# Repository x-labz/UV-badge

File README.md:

# UV-badge

Project site on hackaday.io https://hackaday.io/project/4706-uv-badge 

Twitter: @xLabzNet

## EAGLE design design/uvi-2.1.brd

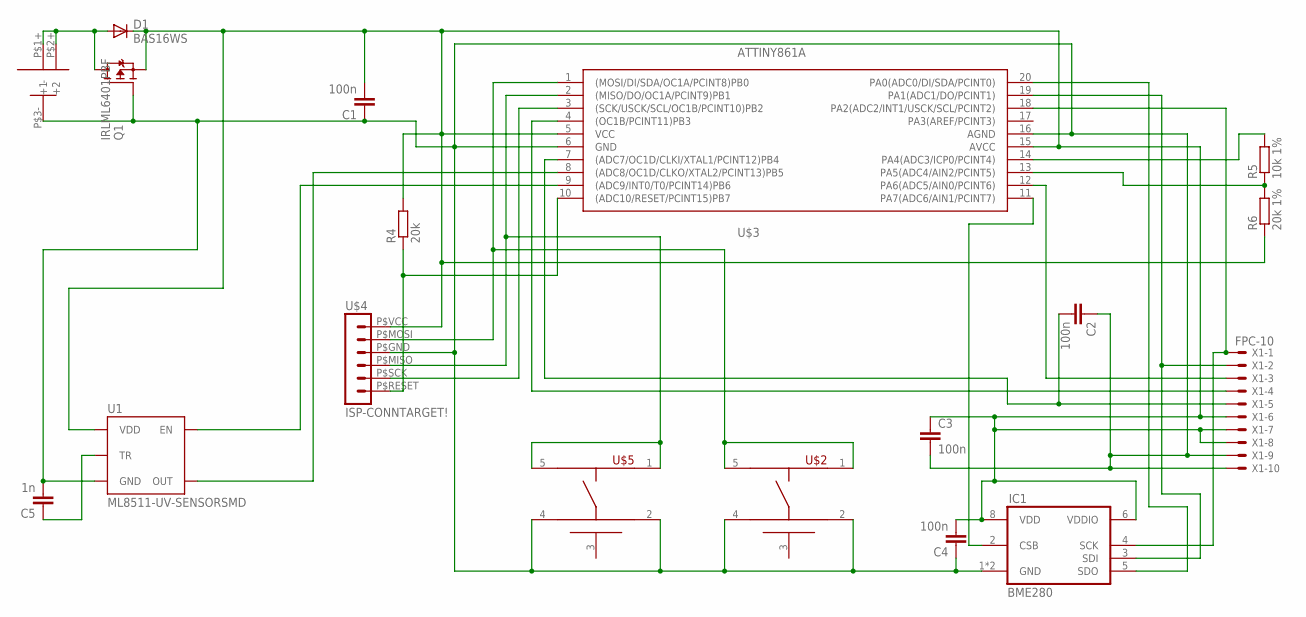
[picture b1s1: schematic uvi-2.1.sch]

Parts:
C1, C2, C3, C4: 100n; C0805
C5: 1n; C0805
D1: BAS16WS; SOD323-W
IC1: BME280; BMP280
Q1: IRLML6401PBF; SOT23
R4: 20k; R0805
R5: 10k 1%; R0805
R6: 20k 1%; R0805
U1: ML8511-UV-SENSORSMD; ML8511
U$1: CR2016; BAT-HLD-002
U$2, U$5: KMSXXXG; C&K-KMS-SWITCH
U$3: ATTINY861A; TSSOP20
U$4: ISP-CONNTARGET!; ISP-TARGET
X1: FPC-10; FPC-10-BTM

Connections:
GND: C1.1, C2.1, C3.2, C4.1, C5.2, IC1.1 (GND), IC1.7 (GND), Q1.1 (G), U1.5 (GND), U$1.P$3- (-), U$2.2, U$2.4, U$3.6 (GND), U$3.16 (AGND), U$4.P$GND (GND), U$5.2, U$5.4, X1.P$9, X1.P$10
unnamed: D1.A, Q1.3 (D), U$1.P$1+ (+1), U$1.P$2+ (+2)
unnamed: R4.1, U$3.10 ((ADC10/RESET/PCINT15)PB7), U$4.P$RESET (RESET)
unnamed: IC1.5 (SDO), U$3.20 (PA0(ADC0/DI/SDA/PCINT0))
unnamed: R5.2, U$3.14 (PA4(ADC3/ICP0/PCINT4))
unnamed: IC1.4 (SCK), U$3.18 (PA2(ADC2/INT1/USCK/SCL/PCINT2)), X1.P$1
unnamed: C5.1, U1.10 (TR)
unnamed: IC1.3 (SDI), U$3.19 (PA1(ADC1/DO/PCINT1)), X1.P$2
unnamed: U1.8 (OUT), U$3.8 ((ADC8/OC1D/CLKO/XTAL2/PCINT13)PB5)
unnamed: C2.2, U$3.7 ((ADC7/OC1D/CLKI/XTAL1/PCINT12)PB4), X1.P$5
unnamed: U$3.2 ((MISO/DO/OC1A/PCINT9)PB1), U$4.P$MISO (MISO), U$5.1, U$5.5
unnamed: U$3.3 ((SCK/USCK/SCL/OC1B/PCINT10)PB2), U$4.P$SCK (SCK)
unnamed: IC1.2 (CSB), U$3.11 (PA7(ADC6/AIN1/PCINT7))
unnamed: U$3.4 ((OC1B/PCINT11)PB3), X1.P$4
unnamed: U$3.12 (PA6(ADC5/AIN0/PCINT6)), X1.P$3
unnamed: U$2.1, U$2.5, U$3.1 ((MOSI/DI/SDA/OC1A/PCINT8)PB0), U$4.P$MOSI (MOSI)
unnamed: U1.4 (EN), U$3.9 ((ADC9/INT0/T0/PCINT14)PB6)
unnamed: R5.1, R6.2, U$3.13 (PA5(ADC4/AIN2/PCINT5))
VCC: C1.2, C3.1, C4.2, D1.C, IC1.6 (VDDIO), IC1.8 (VDD), Q1.2 (S), R4.2, R6.1, U1.7 (VDD), U$3.5 (VCC), U$3.15 (AVCC), U$4.P$VCC (VCC), X1.P$6, X1.P$7, X1.P$8

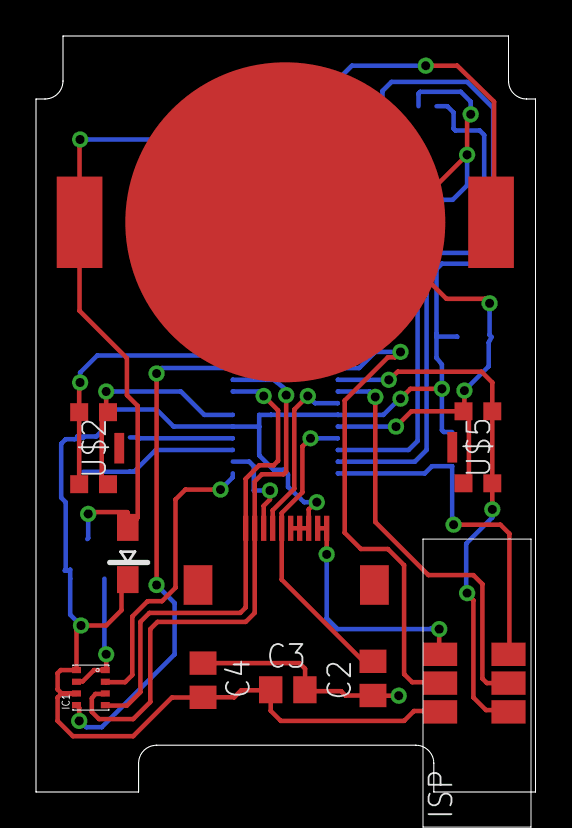
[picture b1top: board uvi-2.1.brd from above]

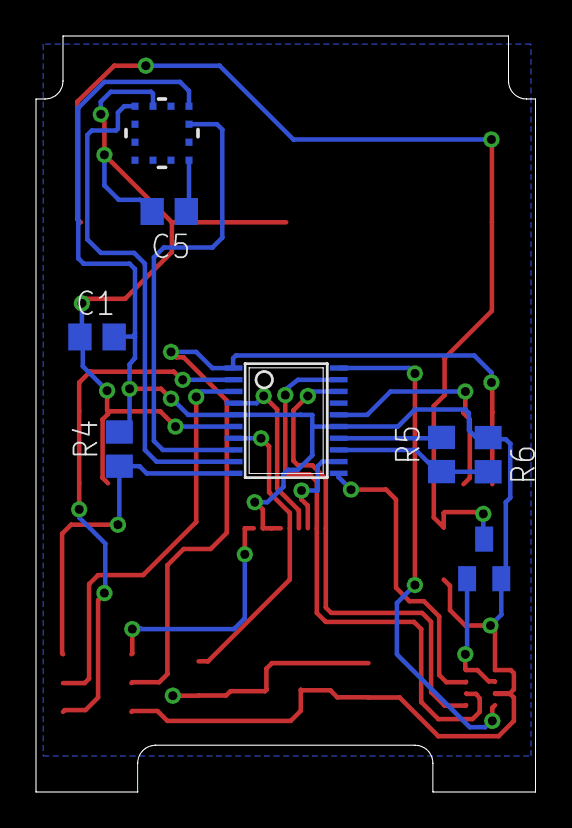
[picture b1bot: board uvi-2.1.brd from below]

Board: 2 copper layers, 27.8 x 42.0 mm, 18 parts (8 on the bottom side), 19 nets.

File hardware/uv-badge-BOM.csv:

"Qty";"Value";"Device";"Package";"Parts";"Description";"PROD_ID";
"4";"100n";"C-EUC0805";"C0805";"C1, C2, C3, C4";"CAPACITOR, European symbol";"";
"1";"10k 1%";"R-EU_R0805";"R0805";"R5";"RESISTOR, European symbol";"";
"1";"1n";"C-EUC0805";"C0805";"C5";"CAPACITOR, European symbol";"";
"1";"20k";"R-EU_R0805";"R0805";"R4";"RESISTOR, European symbol";"";
"1";"20k 1%";"R-EU_R0805";"R0805";"R6";"RESISTOR, European symbol";"";
"1";"ATTINY861A";"ATTINY861A";"TSSOP20";"U$3";"";"";
"1";"BAS16WS";"BAS16WS";"SOD323-W";"D1";"DIODE";"";
"1";"BME280";"BME280";"BMP280";"IC1";"The BMP280 is an absolute barometric pressure sensor especially designed for mobile applications. The sensor module is housed in an extremely compact 8-pin metal-lid LGA package with a footprint of only 2.0 × 2.5 mm2 and 0.95 mm package height. Its small";"";
"1";"CR2016";"CR2016";"BAT-HLD-002";"U$1";"";"";
"1";"FPC-10";"FPC-10";"FPC-10-BTM";"X1";"FPC Connector ZIF for SMT 0.5mm";"";
"1";"IRLML6401PBF";"IRLML6401PBF";"SOT23";"Q1";"";"";
"1";"ISP-CONNTARGET!";"ISP-CONNTARGET!";"ISP-TARGET";"U$4";"6 x 0.1 inch Header";"";
"2";"KMSXXXG";"KMSXXXG";"C&K-KMS-SWITCH";"U$2, U$5";"C&K KMS Series";"";
"1";"ML8511-UV-SENSORSMD";"ML8511-UV-SENSORSMD";"ML8511";"U1";"";"IC-11927";

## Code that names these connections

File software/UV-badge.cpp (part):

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	PORTB = 0x03;
	
	//SET_BIT(DDRB,PINB3); // OC1B out
	//SET_BIT(DDRB,PINB4); // PB4 out (disp)
	//SET_BIT(DDRB,PINB6); // PB6 out (UV en)
	DDRB = 0b01011000 ;
	
	//SET_BIT(DDRA,PINA1); // PA1 out (spi DO)
	//SET_BIT(DDRA,PINA2); // PA2 out (spi SCL)
	//SET_BIT(DDRA,PINA4); // PA4 out (batt EN)	
	//SET_BIT(DDRA,PINA6); // PA6 out (LCD CS)
	//SET_BIT(DDRA,PINA7); // PA7 out (sensor CS)
	DDRA = 0b11010110;
	
	//SET_BIT(PORTA,PINA4); // batt.EN -->H
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
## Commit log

2015-07-14 Update LICENSE
2015-07-14 Create license
2015-07-29 design files
2015-07-29 firmware
2015-07-29 hardware
2015-08-15 system design doc
2015-08-31 prog-adapter
2016-06-06 v4.0

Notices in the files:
parts and their libraries:
SparkFun-Sensors: Licensing: Creative Commons ShareAlike 4.0 International - https://creativecommons.org/licenses/by-sa/4.0
